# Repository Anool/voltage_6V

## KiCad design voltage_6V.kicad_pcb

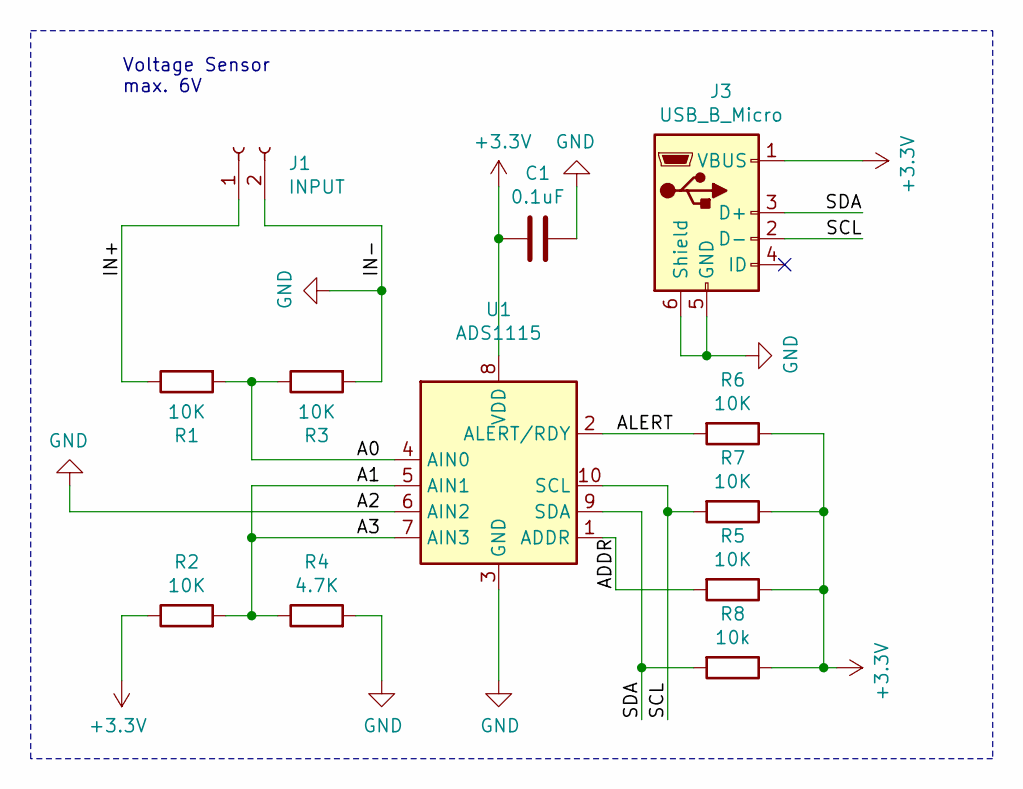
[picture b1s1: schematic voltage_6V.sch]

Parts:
C1: 0.1uF; C_0402_1005Metric
J1: INPUT; PinHeader_1x02_P2.54mm_Vertical
J3: USB_B_Micro; USB_Micro-B_GCT_USB3076-30-A
R1, R2, R3, R5, R6, R7: 10K; R_0402_1005Metric
R4: 4.7K; R_0402_1005Metric
R8: 10k; R_0402_1005Metric
U1: ADS1115; TSSOP-10_3x3mm_P0.5mm

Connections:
+3V3: C1.2, J3.1 (VBUS), R2.1, R5.1, R6.1, R7.1, R8.1, U1.8 (VDD)
/A0: R1.2, R3.1, U1.4 (AIN0)
/A1: R2.2, R4.1, U1.5 (AIN1), U1.7 (AIN3)
/ADDR: R5.2, U1.1 (ADDR)
/ALERT: R6.2, U1.2 (ALERT/RDY)
/IN+: J1.1, R1.1
/SCL: J3.2 (D-), R7.2, U1.10 (SCL)
/SDA: J3.3 (D+), R8.2, U1.9 (SDA)
GND: C1.1, J1.2, J3.5 (GND), J3.6 (Shield), R3.2, R4.2, U1.3 (GND), U1.6 (AIN2)

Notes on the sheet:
Voltage Sensor max. 6V

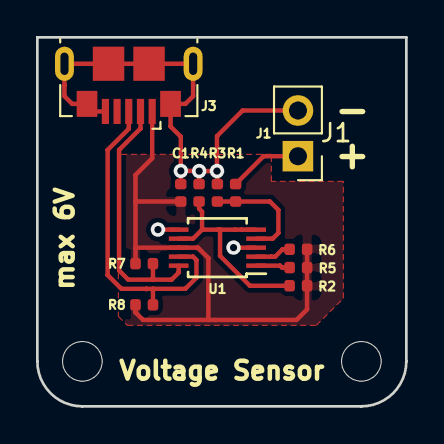
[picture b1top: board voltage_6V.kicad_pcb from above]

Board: 2 copper layers, 20.5 x 20.5 mm, 12 parts (0 on the bottom side), 9 nets.

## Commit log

2018-12-16 voltage sensor breakout
